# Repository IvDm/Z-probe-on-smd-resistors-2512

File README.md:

# Z-probe-on-smd-resistors-2512
 This project is based on a change in the resistance of resistors under the influence of external factors in particular deformation. The object of the project is to check whether it is possible to use ordinary smd resistors instead of strain gages, and apply this effect to the calibration of the bed 3d printer.
 To implement the project I needed: 4 smd resistor with a resistance of 1 kOhm size 2512, ADC HX711, microcontroller ATtiny 85,pnp transistor bc 807-40 sot23,resistors of size 0805 with a rating of 8.2 kΩ 1 pcs., 22 kΩ 1 pcs., 2.2 kΩ 1 pcs.,capacitors 0805 with a capacity of 4.7u 1pcs, 1u 2pcs, 100n 1pcs, LED 0603 any color 1pcs.,double sided copper clad plate PCB, 3d printer for making plastic parts.Library for the HX711 from here: https://github.com/bogde/HX711
 
 As a result, on a double-sided printed circuit board such a sensor was made:

To reduce side effects, the resistors are placed on a two-sided printed circuit board diagonally from both sides. So the sensitivity at the midpoint turned out to be maximum with vertical exposure.To reduce the length of conductors coming from the sensor, it was decided to make a small circuit board for signal processing and place it directly on the sensor board. On the one side of the board is the ADC of the HX711, and on the other the microcontroller ATtiny85.

From the microcontroller, the touch signal is fed to the 3-d printer board.

The boards are interconnected in this way:

To install the sensor on a 3d printer, the following parts were printed:

They are assembled in this way:

assembled:

I have a 3d printer "HyperCube" https://www.thingiverse.com/thing:1752766 and installed a sensor on this printer. 
It looks like this:

This is how it looks in action:

https://www.youtube.com/watch?v=x-7hq27BdUY&t=6s

Thus, testing was carried out on the suitability of using SMD resistors for use in the sensor):

https://www.youtube.com/watch?v=UKC9-srKAL4

Oh, and sorry for my English)

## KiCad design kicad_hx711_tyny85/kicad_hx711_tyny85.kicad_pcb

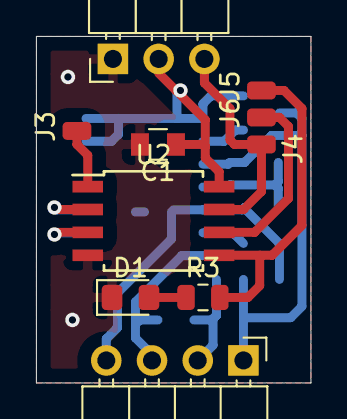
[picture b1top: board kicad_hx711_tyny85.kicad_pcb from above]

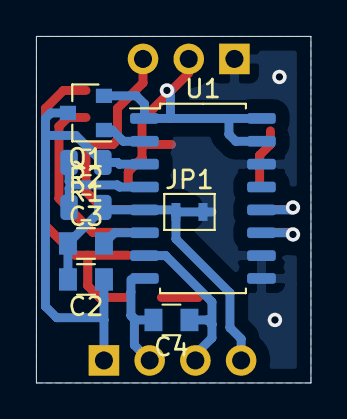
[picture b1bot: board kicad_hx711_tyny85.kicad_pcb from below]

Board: 2 copper layers, 15.2 x 19.2 mm, 18 parts (8 on the bottom side), 16 nets.

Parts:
C1: 4.7u; C_0805
C2, C3: 1u; C_0805
C4: 0.1u; C_0805
D1: LED; LED_0805_2012Metric_Pad1.15x1.40mm_HandSolder
J1: Conn_01x03_Male; Pin_Header_Angled_1x03_Pitch2.54mm
J2: Conn_01x04_Female; Pin_Header_Angled_1x04_Pitch2.54mm
J3, J4, J5, J6: Conn_01x01_Female; SMD_wire_conn
JP1: Jumper; AnalogGND_jumper
Q1: Q_PNP_BEC; SOT-23
R1: 22k; R_0805_2012Metric
R2: 8k2; R_0805_2012Metric
R3: 2k2; R_0805_2012Metric
U1: HX711; SOP-16_4.55x10.3mm_P1.27mm
U2: ATtiny85V-10SU; SOIJ-8_5.3x5.3mm_P1.27mm

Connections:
DOUT: U1.12, U2.2
GND: C1.2, D1.1, J1.1, JP1.2, U1.9, U1.10, U1.14, U2.4
GNDA: C2.2, C3.1, J2.4, JP1.1, R2.2, U1.5
INNA: C4.1, J2.3, U1.7
INPA: C4.2, J2.2, U1.8
MISO: J6.1, U2.6
MOSI: J5.1, R3.2, U2.5
unnamed: C3.2, U1.6
unnamed: D1.2, R3.1
unnamed: Q1.1, U1.2
unnamed: R1.2, R2.1, U1.4
RST: J3.1, U2.1
SCK: U1.11, U2.3
SCK_OUT: J1.3, J4.1, U2.7
VCC: C1.1, J1.2, Q1.2, U1.1, U1.15, U1.16, U2.8
VDDA: C2.1, J2.1, Q1.3, R1.1, U1.3

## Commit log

2018-10-01 Create LICENSE
2018-10-03 Set theme jekyll-theme-cayman
2020-06-02 Update fp-info-cache, kicad_hx711_tyny85-cache.lib, and 4 more files...
2020-06-02 Split GND-AGND
